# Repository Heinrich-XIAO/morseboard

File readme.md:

# Morseboard

My hackpad keyboard is a keyboard that types in morse code. The rotary encoder is for volume. I was inspired to do this because I kept making smaller and smaller keyboards, and this is the next step in my journey. Maybe one day, I'll make a 1-key keyboard. The reason I chose to use morse code, was because I coincidentally was learning it for fun. This was also my first time truly designing my own keyboard with my previous keyboards just being half of a pre-built split keyboard, so I had to learn how to use real CAD tools.

## Features
- Rotary Encoder
- Morse Code!!
- Screen

## Schematics

## PCB

## Assembly

## BOM

| Qty | Part Name               |
|-----|-------------------------|
| 1   | Rotary Encoder          |
| 6   | Cherry MX Switches      |
| 6   | DSA Keycaps             |
| 1   | 0.91 inch OLED displays |
| 7   | SK6812 MINI-E LEDs      |
| 1   | Seeed XIAO RP2040       |
| 6   | THT 1N4148 Diodes       |
| 1   | Case (3d-printed)       |
| 5   | PCB                     |

## Finished Build

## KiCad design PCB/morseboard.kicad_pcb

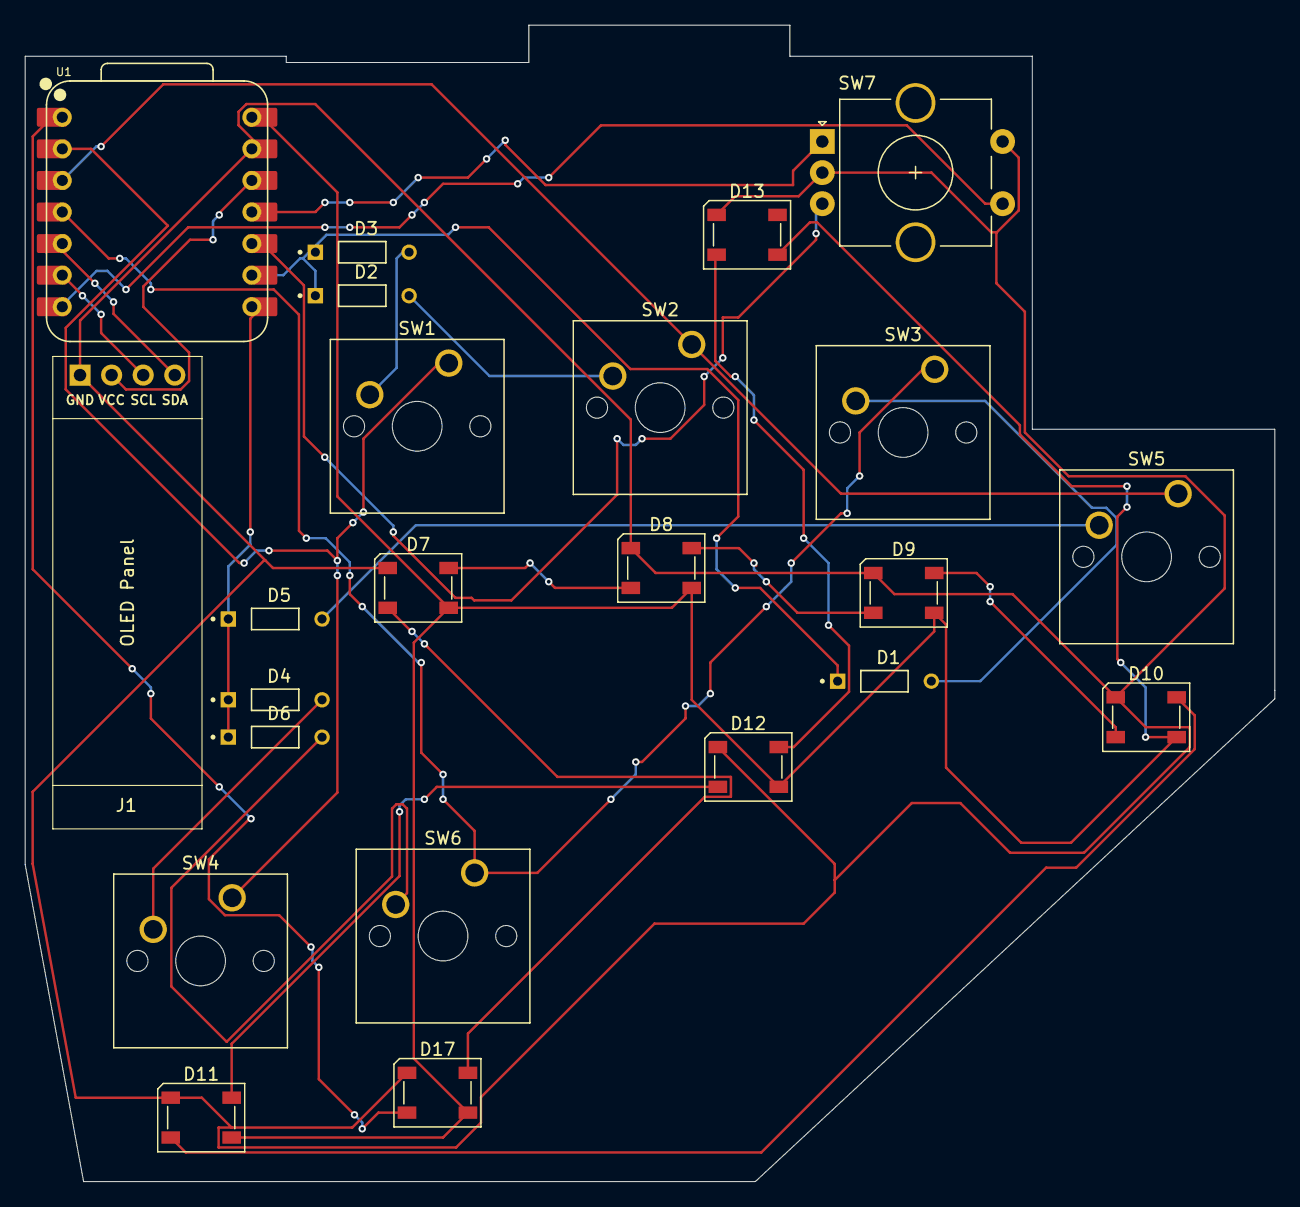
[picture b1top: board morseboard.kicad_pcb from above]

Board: 2 copper layers, 100.5 x 93.0 mm, 23 parts (0 on the bottom side), 27 nets.

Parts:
D1, D2, D3, D4, D5, D6: 1N4148; DIOAD753W49L380D172B
D7, D8, D9, D10, D11, D12, D13, D17: SK6812; LED_SK6812_PLCC4_5.0x5.0mm_P3.2mm
J1: Conn_01x04_Socket; SSD1306-0.91-OLED-4pin-128x32
SW1, SW2, SW3, SW4, SW5, SW6: SW_Push; SW_Cherry_MX_1.00u_PCB
SW7: RotaryEncoder_Switch; RotaryEncoder_Alps_EC11E-Switch_Vertical_H20mm_CircularMoun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
U1: XIAO-RP2040-DIP

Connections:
+3.3V: J1.2, U1.12 (3V3)
+5V: D7.3 (VDD), D8.3 (VDD), D9.3 (VDD), D10.3 (VDD), D11.3 (VDD), D12.3 (VDD), D13.3 (VDD), D17.3 (VDD), U1.14 (VBUS)
GND: D7.1 (VSS), D8.1 (VSS), D9.1 (VSS), D10.1 (VSS), D11.1 (VSS), D12.1 (VSS), D13.1 (VSS), D17.1 (VSS), J1.1, SW7.C, SW7.S2, U1.13 (GND)
unnamed: D1.A, SW3.2
unnamed: D2.A, SW2.2
unnamed: D3.A, SW1.2
unnamed: D4.A, SW4.2
unnamed: D5.A, SW5.2
unnamed: D6.A, SW6.2
unnamed: D7.4 (DOUT), D8.2 (DIN)
unnamed: D8.4 (DOUT), D9.2 (DIN)
unnamed: D9.4 (DOUT), D10.2 (DIN)
unnamed: D10.4 (DOUT), D11.2 (DIN)
unnamed: D11.4 (DOUT), D12.2 (DIN)
unnamed: D12.4 (DOUT), D13.2 (DIN)
unnamed: D17.2 (DIN), U1.1 (GPIO26/ADC0/A0)
unnamed: D7.2 (DIN), D17.4 (DOUT)
unnamed: J1.3, U1.6 (GPIO7/SCL)
unnamed: J1.4, U1.5 (GPIO6/SDA)
unnamed: SW7.S1, U1.7 (GPIO0/TX)
unnamed: D4.K, D5.K, D6.K, U1.8 (GPIO1/RX)
unnamed: D1.K, D2.K, D3.K, U1.9 (GPIO2/SCK)
unnamed: SW7.A, U1.11 (GPIO3/MOSI)
unnamed: SW7.B, U1.10 (GPIO4/MISO)
unnamed: SW1.1, SW4.1, U1.2 (GPIO27/ADC1/A1)
unnamed: SW2.1, SW5.1, U1.3 (GPIO28/ADC2/A2)
unnamed: SW3.1, SW6.1, U1.4 (GPIO29/ADC3/A3)

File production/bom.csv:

Designator,Footprint,Quantity,Value,LCSC Part #
"D1, D2, D3, D4, D5, D6",DIOAD753W49L380D172B,6,1N4148,
"D10, D11, D12, D13, D17, D7, D8, D9",LED_SK6812_PLCC4_5.0x5.0mm_P3.2mm,8,SK6812,
J1,SSD1306-0.91-OLED-4pin-128x32,1,Conn_01x04_Socket,
"SW1, SW2, SW3, SW4, SW5, SW6",SW_Cherry_MX_1.00u_PCB,6,SW_Push,
SW7,RotaryEncoder_Alps_EC11E-Switch_Vertical_H20mm_CircularMountingHoles,1,RotaryEncoder_Switch,
U1,XIAO-RP2040-DIP,1,XIAO-RP2040-DIP,

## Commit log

2025-06-02 pcb and schem and stuff since i forgot to make a git repo before
2025-06-05 pcb done, to add 3d files next commit
2025-06-05 backjournal
2025-06-05 upload full assembly
2025-06-05 assembly done
2025-06-05 keymap is now the actual one
2025-06-05 morse code interpreter
2025-06-06 added the rotary stuff
2025-06-06 screenshots
2025-06-06 add the screenshots
2025-06-06 step version
2025-06-06 organize
2025-06-06 gerbers.zip
2025-06-06 remove unncessary files
2025-06-06 add 3d cad files
2025-06-06 firmware now in prod dir
2025-06-06 now its under the size limit.(before it was 0.55mm too wide)
2025-06-06 corrected some timestamps and added duratoin
2025-06-06 branding
2025-06-08 readme change
2025-08-08 make code work
2025-08-08 update cad
2025-08-08 add image to readme
